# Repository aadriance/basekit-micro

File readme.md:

# Basekit-Micro

Basekit-micro is a 40% keyboard that uses a pro micro and a standard 60% base
kit for it's keys. Want to use a cool keyset and a planck layout? basekit is
here for you!

## Fair Warning

This is my first PCB design. I have built 3 PCBs of this and used them for a
year without issue, that doesn't mean it's perfect. I don't recommend using
it unless you have experience making PCBs from open source repos.

## Making it

- Visit the PCB folder to get the PCB produced.
- Visit the firmware folder to make your layout, or use mine.
- Visit the case folder and choose a case configuration.
- Enjoy.

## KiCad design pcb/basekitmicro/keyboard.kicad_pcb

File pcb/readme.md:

# PCB

- The basekitmicro folder contains the kicad project.
- The jlcpcb folder contains the files I used to get a run made by jlcpcb.

To build the pcb you will need:

- 47 SMD dioides if not using a soldering service. See BOM in jlcpcb folder.
- a pro micro.

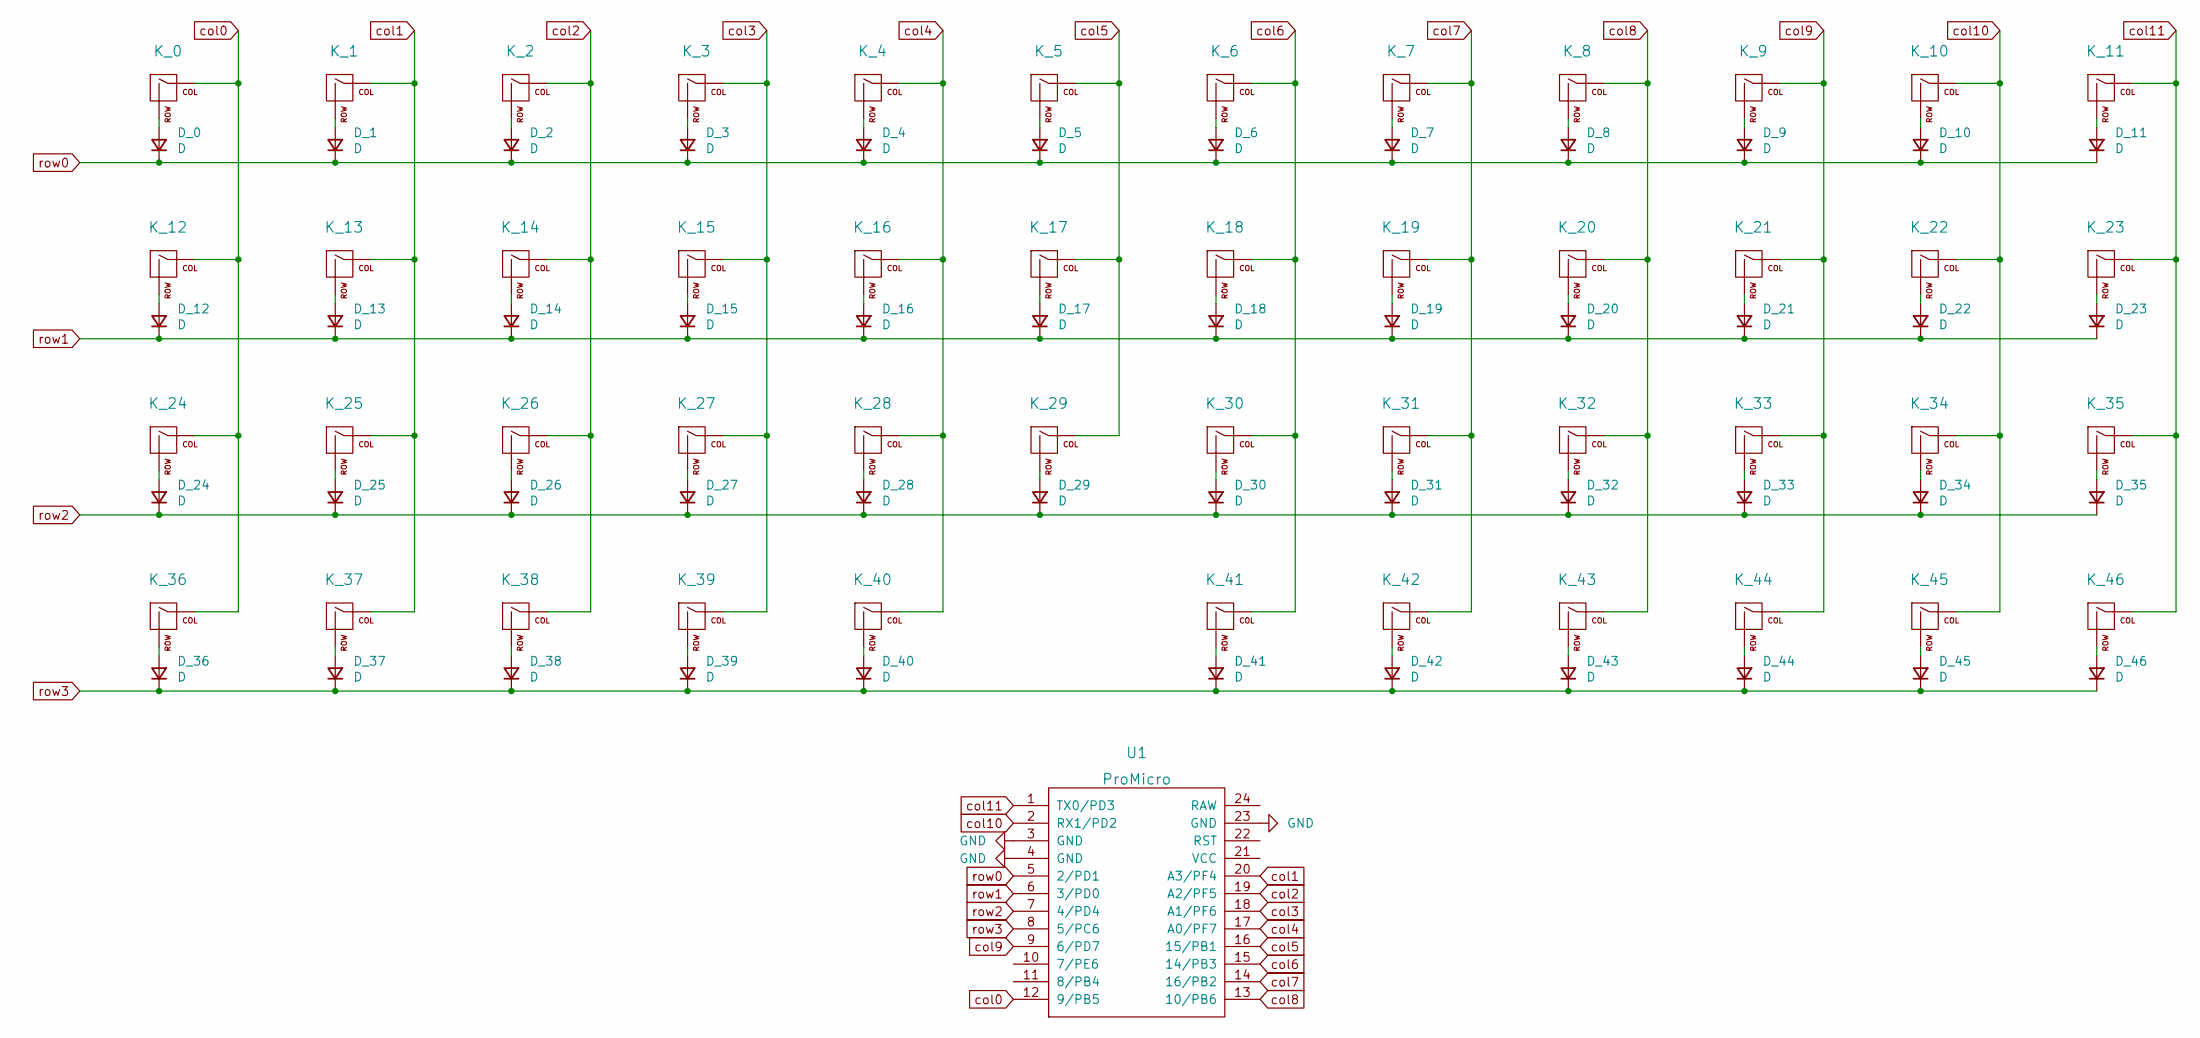
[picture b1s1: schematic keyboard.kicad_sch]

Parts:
D_0, D_1, D_2, D_3, D_4, D_5, D_6, D_7, D_8, D_9, D_10, D_11, D_12, D_13, D_14, D_15, D_16, D_17, D_18, D_19, D_20, D_21, D_22, D_23, D_24, D_25, D_26, D_27, D_28, D_29, D_30, D_31, D_32, D_33, D_34, D_35, D_36, D_37, D_38, D_39, D_40, D_41, D_42, D_43, D_44, D_45, D_46: D; D_SOD-123
K_0, K_11: KEYSW; MX-1.5U-NoLED
K_1, K_2, K_3, K_4, K_5, K_6, K_7, K_8, K_9, K_10, K_13, K_14, K_15, K_16, K_17, K_18, K_19, K_20, K_21, K_22, K_25, K_26, K_27, K_28, K_29, K_30, K_31, K_32, K_33, K_34, K_37, K_38, K_39, K_40, K_42, K_43, K_44, K_45: KEYSW; MX-1U-NoLED
K_12: KEYSW; MX-1.75U-NoLED
K_23, K_24: KEYSW; MX-2.25U-NoLED
K_35: KEYSW; MX-2.75U-NoLED
K_36, K_46: KEYSW; MX-1.25U-NoLED
K_41: KEYSW; MX-2U-NoLED
U1: ProMicro; ArduinoProMicro

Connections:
GND: U1.3 (GND), U1.4 (GND), U1.23 (GND)
unnamed: D_0.2 (A), K_0.2 (ROW)
unnamed: D_1.2 (A), K_1.2 (ROW)
unnamed: D_2.2 (A), K_2.2 (ROW)
unnamed: D_3.2 (A), K_3.2 (ROW)
unnamed: D_4.2 (A), K_4.2 (ROW)
unnamed: D_5.2 (A), K_5.2 (ROW)
unnamed: D_6.2 (A), K_6.2 (ROW)
unnamed: D_7.2 (A), K_7.2 (ROW)
unnamed: D_8.2 (A), K_8.2 (ROW)
unnamed: D_9.2 (A), K_9.2 (ROW)
unnamed: D_10.2 (A), K_10.2 (ROW)
unnamed: D_11.2 (A), K_11.2 (ROW)
unnamed: D_12.2 (A), K_12.2 (ROW)
unnamed: D_13.2 (A), K_13.2 (ROW)
unnamed: D_14.2 (A), K_14.2 (ROW)
unnamed: D_15.2 (A), K_15.2 (ROW)
unnamed: D_16.2 (A), K_16.2 (ROW)
unnamed: D_17.2 (A), K_17.2 (ROW)
unnamed: D_18.2 (A), K_18.2 (ROW)
unnamed: D_19.2 (A), K_19.2 (ROW)
unnamed: D_20.2 (A), K_20.2 (ROW)
unnamed: D_21.2 (A), K_21.2 (ROW)
unnamed: D_22.2 (A), K_22.2 (ROW)
unnamed: D_23.2 (A), K_23.2 (ROW)
unnamed: D_24.2 (A), K_24.2 (ROW)
unnamed: D_25.2 (A), K_25.2 (ROW)
unnamed: D_26.2 (A), K_26.2 (ROW)
unnamed: D_27.2 (A), K_27.2 (ROW)
unnamed: D_28.2 (A), K_28.2 (ROW)
unnamed: D_29.2 (A), K_29.2 (ROW)
unnamed: D_30.2 (A), K_30.2 (ROW)
unnamed: D_31.2 (A), K_31.2 (ROW)
unnamed: D_32.2 (A), K_32.2 (ROW)
unnamed: D_33.2 (A), K_33.2 (ROW)
unnamed: D_34.2 (A), K_34.2 (ROW)
unnamed: D_35.2 (A), K_35.2 (ROW)
unnamed: D_36.2 (A), K_36.2 (ROW)
unnamed: D_37.2 (A), K_37.2 (ROW)
unnamed: D_38.2 (A), K_38.2 (ROW)
unnamed: D_39.2 (A), K_39.2 (ROW)
unnamed: D_40.2 (A), K_40.2 (ROW)
unnamed: D_41.2 (A), K_41.2 (ROW)
unnamed: D_42.2 (A), K_42.2 (ROW)
unnamed: D_43.2 (A), K_43.2 (ROW)
unnamed: D_44.2 (A), K_44.2 (ROW)
unnamed: D_45.2 (A), K_45.2 (ROW)
unnamed: D_46.2 (A), K_46.2 (ROW)
col0: K_0.1 (COL), K_12.1 (COL), K_24.1 (COL), K_36.1 (COL), U1.12 (9/PB5)
col1: K_1.1 (COL), K_13.1 (COL), K_25.1 (COL), K_37.1 (COL), U1.20 (A3/PF4)
col2: K_2.1 (COL), K_14.1 (COL), K_26.1 (COL), K_38.1 (COL), U1.19 (A2/PF5)
col3: K_3.1 (COL), K_15.1 (COL), K_27.1 (COL), K_39.1 (COL), U1.18 (A1/PF6)
col4: K_4.1 (COL), K_16.1 (COL), K_28.1 (COL), K_40.1 (COL), U1.17 (A0/PF7)
col5: K_5.1 (COL), K_17.1 (COL), K_29.1 (COL), U1.16 (15/PB1)
col6: K_6.1 (COL), K_18.1 (COL), K_30.1 (COL), K_41.1 (COL), U1.15 (14/PB3)
col7: K_7.1 (COL), K_19.1 (COL), K_31.1 (COL), K_42.1 (COL), U1.14 (16/PB2)
col8: K_8.1 (COL), K_20.1 (COL), K_32.1 (COL), K_43.1 (COL), U1.13 (10/PB6)
col9: K_9.1 (COL), K_21.1 (COL), K_33.1 (COL), K_44.1 (COL), U1.9 (6/PD7)
col10: K_10.1 (COL), K_22.1 (COL), K_34.1 (COL), K_45.1 (COL), U1.2 (RX1/PD2)
col11: K_11.1 (COL), K_23.1 (COL), K_35.1 (COL), K_46.1 (COL), U1.1 (TX0/PD3)
row0: D_0.1 (K), D_1.1 (K), D_2.1 (K), D_3.1 (K), D_4.1 (K), D_5.1 (K), D_6.1 (K), D_7.1 (K), D_8.1 (K), D_9.1 (K), D_10.1 (K), D_11.1 (K), U1.5 (2/PD1)
row1: D_12.1 (K), D_13.1 (K), D_14.1 (K), D_15.1 (K), D_16.1 (K), D_17.1 (K), D_18.1 (K), D_19.1 (K), D_20.1 (K), D_21.1 (K), D_22.1 (K), D_23.1 (K), U1.6 (3/PD0)
row2: D_24.1 (K), D_25.1 (K), D_26.1 (K), D_27.1 (K), D_28.1 (K), D_29.1 (K), D_30.1 (K), D_31.1 (K), D_32.1 (K), D_33.1 (K), D_34.1 (K), D_35.1 (K), U1.7 (4/PD4)
row3: D_36.1 (K), D_37.1 (K), D_38.1 (K), D_39.1 (K), D_40.1 (K), D_41.1 (K), D_42.1 (K), D_43.1 (K), D_44.1 (K), D_45.1 (K), D_46.1 (K), U1.8 (5/PC6)

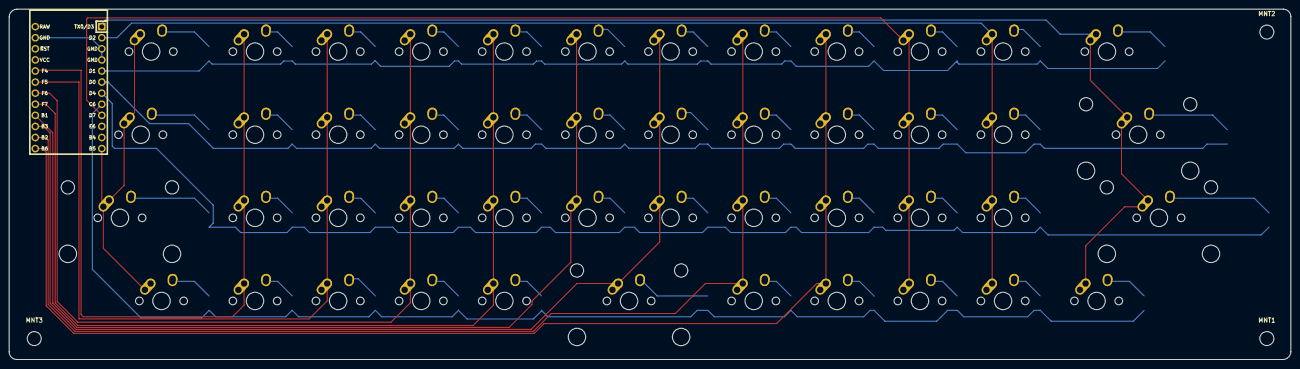
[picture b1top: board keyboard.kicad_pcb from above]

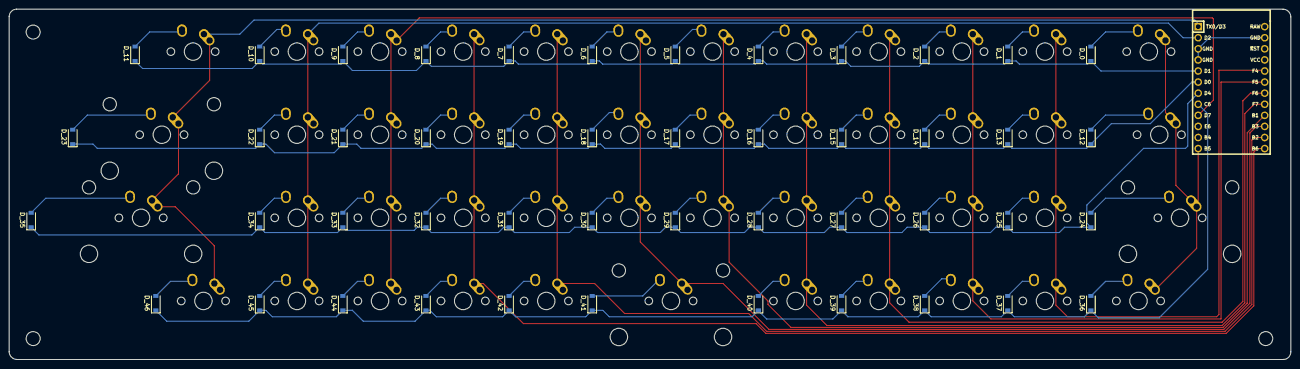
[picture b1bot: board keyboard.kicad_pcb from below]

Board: 2 copper layers, 293.8 x 80.3 mm, 98 parts (48 on the bottom side), 64 nets.

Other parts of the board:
MNT1, MNT2, MNT3: MountingHole_3.2mm_M3

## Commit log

2024-02-25 add cases
2024-02-25 ignore
2024-02-25 firmware
2024-02-25 readme
